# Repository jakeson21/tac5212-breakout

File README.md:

# tac5212_breakout
Breakout board for TAC5212

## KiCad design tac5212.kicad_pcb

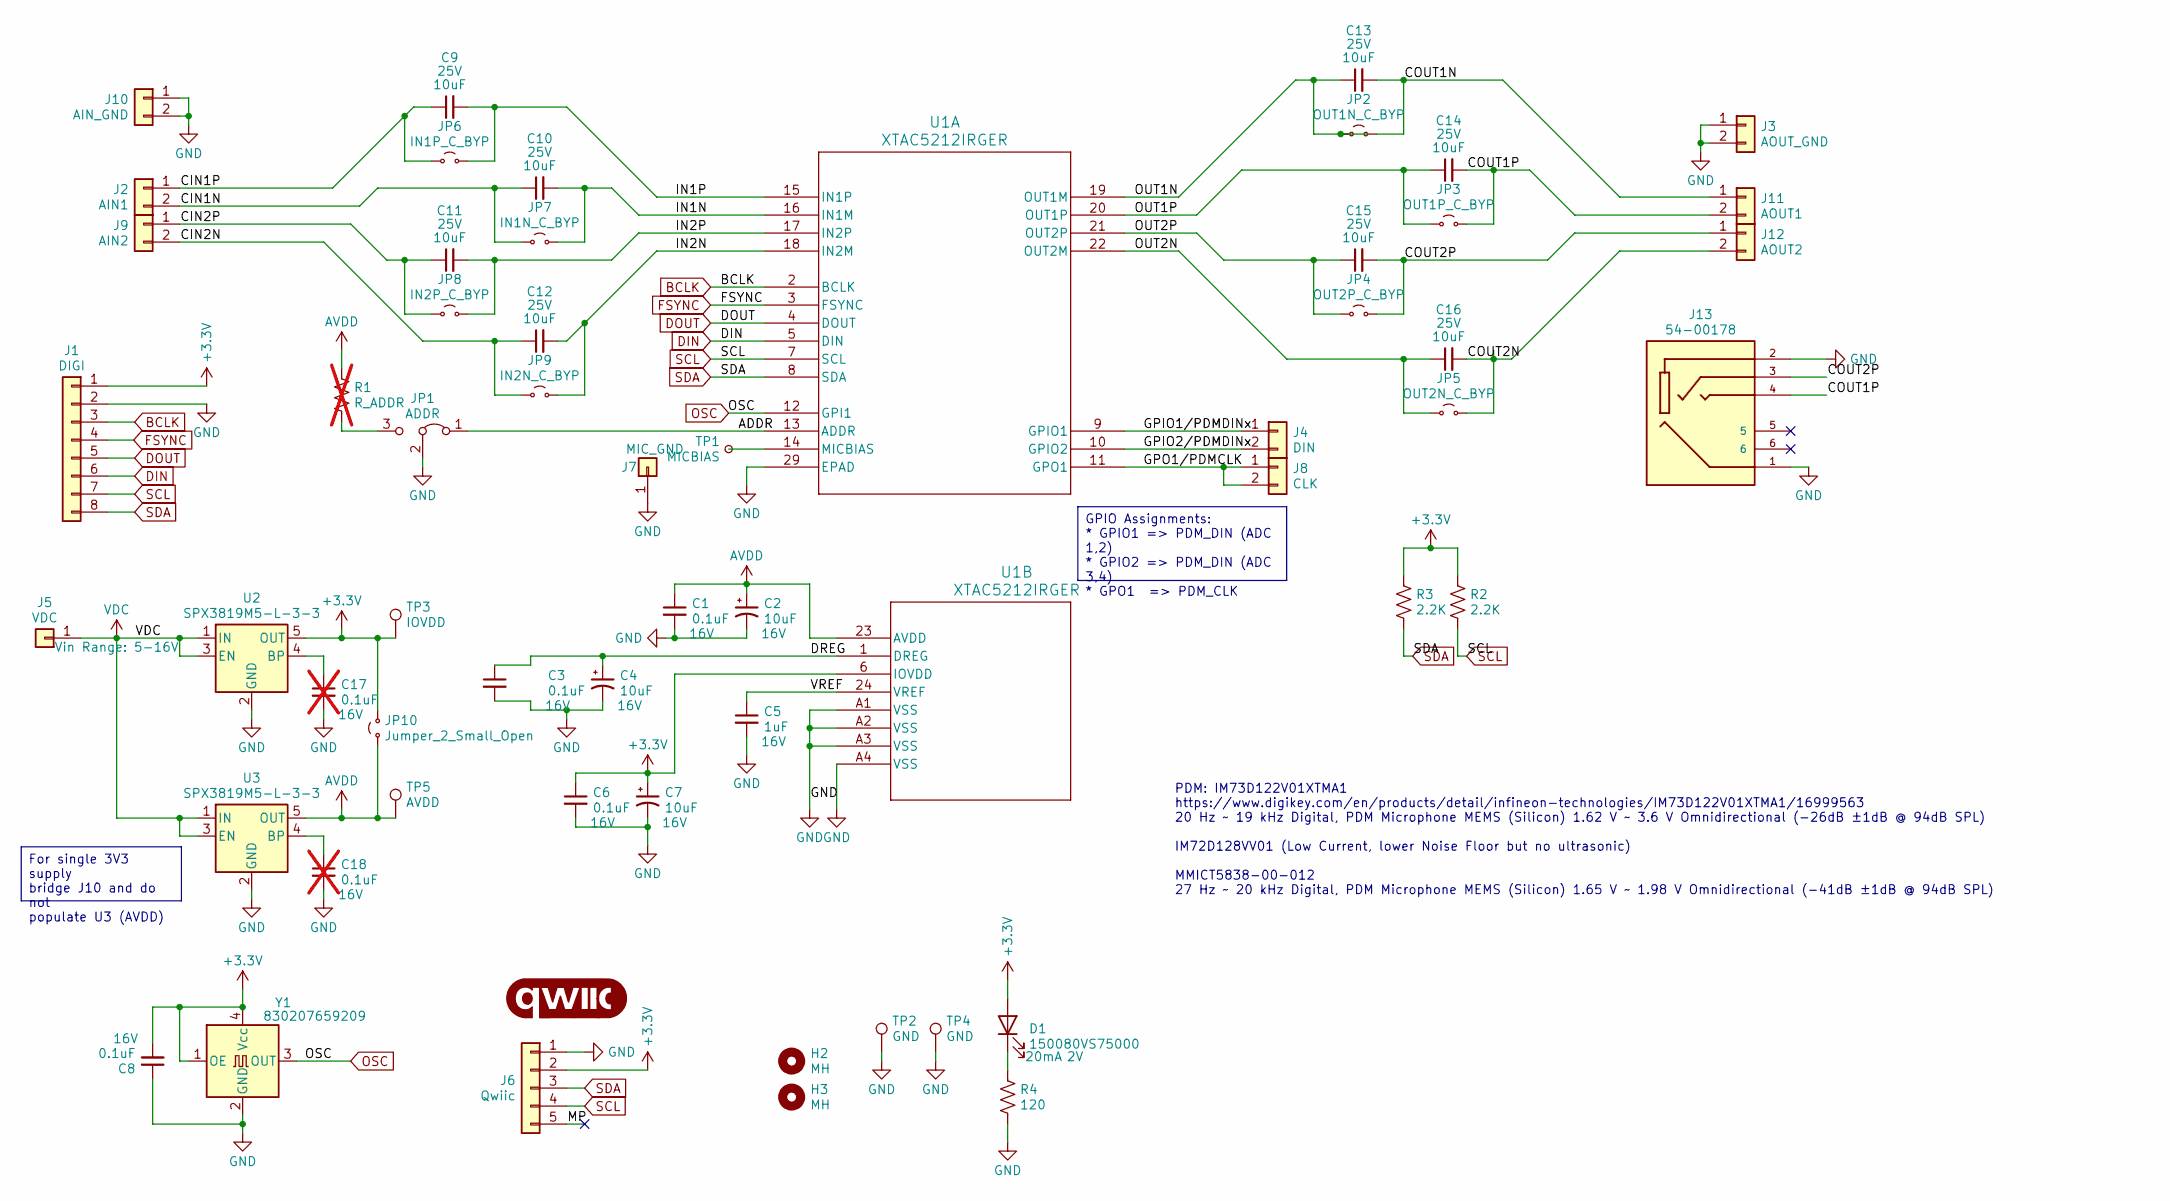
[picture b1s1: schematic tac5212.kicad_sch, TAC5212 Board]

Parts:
C1, C3, C6, C8: 0.1uF; C_0805_2012Metric
C2, C4, C7: 10uF; CP_EIA-3216-10_Kemet-I
C5: 1uF; C_0805_2012Metric
C9, C10, C11, C12, C13, C14, C15, C16: 10uF; C_0805_2012Metric
C17, C18: 0.1uF; C_0805_2012Metric; not fitted
D1: 150080VS75000; LED_0805_2012Metric
G1: qwiic_Logo
H2, H3: MH; MountingHole_2.2mm_M2
J1: DIGI; PinHeader_1x08_P2.54mm_Vertical
J2: AIN1; PinHeader_1x02_P2.54mm_Vertical
J3: AOUT_GND; PinHeader_1x02_P2.54mm_Vertical
J4: DIN; PinHeader_1x02_P2.54mm_Vertical
J5: VDC; PinHeader_1x01_P2.54mm_Vertical
J6: Qwiic; JST_SH_SM04B-SRSS-TB_1x04-1MP_P1.00mm_Horizontal
J7: MIC_GND; PinHeader_1x01_P2.54mm_Vertical
J8: CLK; PinHeader_1x02_P2.54mm_Vertical
J9: AIN2; PinHeader_1x02_P2.54mm_Vertical
J10: AIN_GND; PinHeader_1x02_P2.54mm_Vertical
J11: AOUT1; PinHeader_1x02_P2.54mm_Vertical
J12: AOUT2; PinHeader_1x02_P2.54mm_Vertical
J13: 54-00178; TENSILITY_54-00178; PARTREV A
JP1: ADDR; SolderJumper-3_P1.3mm_Bridged12_RoundedPad1.0x1.5mm_NumberL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
JP2: OUT1N_C_BYP; PinHeader_1x02_P2.54mm_Vertical
JP3: OUT1P_C_BYP; PinHeader_1x02_P2.54mm_Vertical
JP4: OUT2P_C_BYP; PinHeader_1x02_P2.54mm_Vertical
JP5: OUT2N_C_BYP; PinHeader_1x02_P2.54mm_Vertical
JP6: IN1P_C_BYP; PinHeader_1x02_P2.54mm_Vertical
JP7: IN1N_C_BYP; PinHeader_1x02_P2.54mm_Vertical
JP8: IN2P_C_BYP; PinHeader_1x02_P2.54mm_Vertical
JP9: IN2N_C_BYP; PinHeader_1x02_P2.54mm_Vertical
JP10: Jumper_2_Small_Open; SolderJumper-2_P1.3mm_Open_TrianglePad1.0x1.5mm
R1: R_ADDR; R_0805_2012Metric; not fitted
R2, R3: 2.2K; R_0805_2012Metric
R4: 120; R_0805_2012Metric
TP1: MICBIAS; TestPoint_THTPad_D1.5mm_Drill0.7mm
TP2, TP4: GND; 1030
TP3: IOVDD; TestPoint_THTPad_D1.0mm_Drill0.5mm
TP5: AVDD; TestPoint_THTPad_D1.0mm_Drill0.5mm
U1: XTAC5212IRGER; VQFN24_RGE_CORNERPADS_TEX
U2, U3: SPX3819M5-L-3-3; SOT-23-5
Y1: 830207659209; Oscillator_SMD_SeikoEpson_SG8002CE-4Pin_3.2x2.5mm

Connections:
+3.3V: C6.1, C7.1, C8.2, D1.2 (A), J1.1, J6.2, JP10.2 (B), R2.1, R3.1, TP3.1, U1.6 (IOVDD), U2.5 (OUT), Y1.1 (OE), Y1.4 (Vcc)
/ADDR: JP1.1 (A), U1.13 (ADDR)
/CIN1N: C10.1, J2.2, JP7.1 (A)
/CIN1P: C9.1, J2.1, JP6.1 (A)
/CIN2N: C12.1, J9.2, JP9.1 (A)
/CIN2P: C11.1, J9.1, JP8.1 (A)
/COUT1N: C13.2, J11.1, JP2.2 (B)
/COUT1P: C14.2, J11.2, J13.4, JP3.2 (B)
/COUT2N: C16.2, J12.2, JP5.2 (B)
/COUT2P: C15.2, J12.1, J13.3, JP4.2 (B)
/DREG: C3.1, C4.1, U1.1 (DREG)
/GPIO1/PDMDINx: J4.1, U1.9 (GPIO1)
/GPIO2/PDMDINx: J4.2, U1.10 (GPIO2)
/GPO1/PDMCLK: J8.1, J8.2, U1.11 (GPO1)
/IN1N: C10.2, JP7.2 (B), U1.16 (IN1M)
/IN1P: C9.2, JP6.2 (B), U1.15 (IN1P)
/IN2N: C12.2, JP9.2 (B), U1.18 (IN2M)
/IN2P: C11.2, JP8.2 (B), U1.17 (IN2P)
/OUT1N: C13.1, JP2.1 (A), U1.19 (OUT1M)
/OUT1P: C14.1, JP3.1 (A), U1.20 (OUT1P)
/OUT2N: C16.1, JP5.1 (A), U1.22 (OUT2M)
/OUT2P: C15.1, JP4.1 (A), U1.21 (OUT2P)
/VREF: C5.1, U1.24 (VREF)
AVDD: C1.1, C2.1, JP10.1 (A), R1.1, TP5.1, U1.23 (AVDD), U3.5 (OUT)
BCLK: J1.3, U1.2 (BCLK)
DIN: J1.6, U1.5 (DIN)
DOUT: J1.5, U1.4 (DOUT)
FSYNC: J1.4, U1.3 (FSYNC)
GND: C1.2, C2.2, C3.2, C4.2, C5.2, C6.2, C7.2, C8.1, C17.2, C18.2, J1.2, J3.1, J3.2, J6.1, J7.1, J10.1, J10.2, J13.1, J13.2, JP1.2 (C), R4.2, TP2.1, TP4.1, U1.29 (EPAD), U1.A1 (VSS), U1.A2 (VSS), U1.A3 (VSS), U1.A4 (VSS), U2.2 (GND), U3.2 (GND), Y1.2 (GND)
unnamed: D1.1 (K), R4.1
unnamed: JP1.3 (B), R1.2
unnamed: TP1.1, U1.14 (MICBIAS)
unnamed: C17.1, U2.4 (BP)
unnamed: C18.1, U3.4 (BP)
OSC: U1.12 (GPI1), Y1.3 (OUT)
SCL: J1.7, J6.4, R2.2, U1.7 (SCL)
SDA: J1.8, J6.3, R3.2, U1.8 (SDA)
VDC: J5.1, U2.1 (IN), U2.3 (EN), U3.1 (IN), U3.3 (EN)

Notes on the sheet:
PDM: IM73D122V01XTMA1 https://www.digikey.com/en/products/detail/infineon-technologies/IM73D122V01XTMA1/16999563 20 Hz ~ 19 kHz Digital, PDM Microphone MEMS (Silicon) 1.62 V ~ 3.6 V Omnidirectional (-26dB ±1dB @ 94dB SPL) IM72D128VV01 (Low Current, lower Noise Floor but no ultrasonic) MMICT5838-00-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
For single 3V3 supply bridge J10 and do not populate U3 (AVDD)
GPIO Assignments: * GPIO1 => PDM_DIN (ADC 1,2) * GPIO2 => PDM_DIN (ADC 3,4) * GPO1 => PDM_CLK

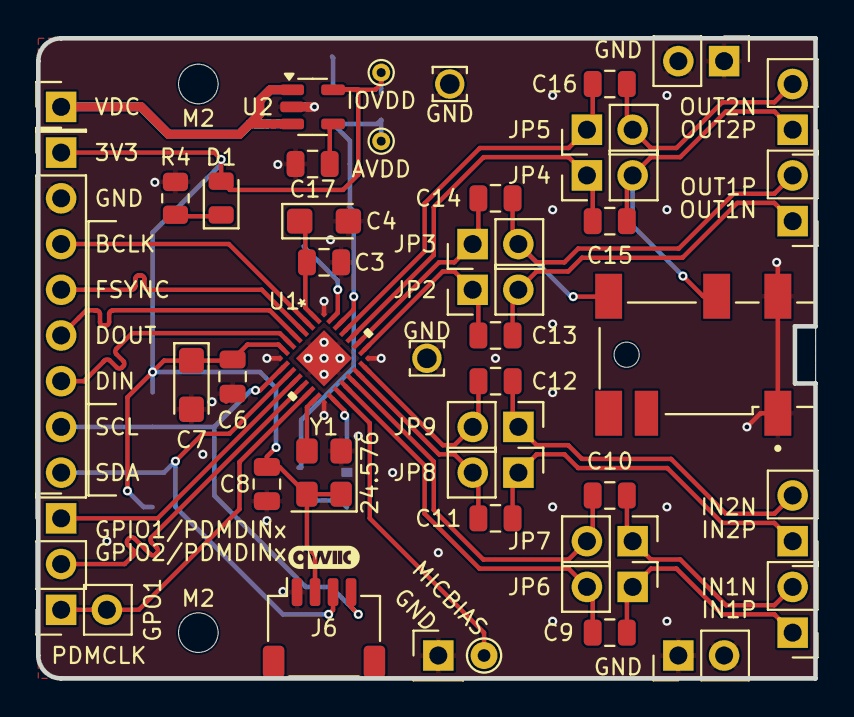
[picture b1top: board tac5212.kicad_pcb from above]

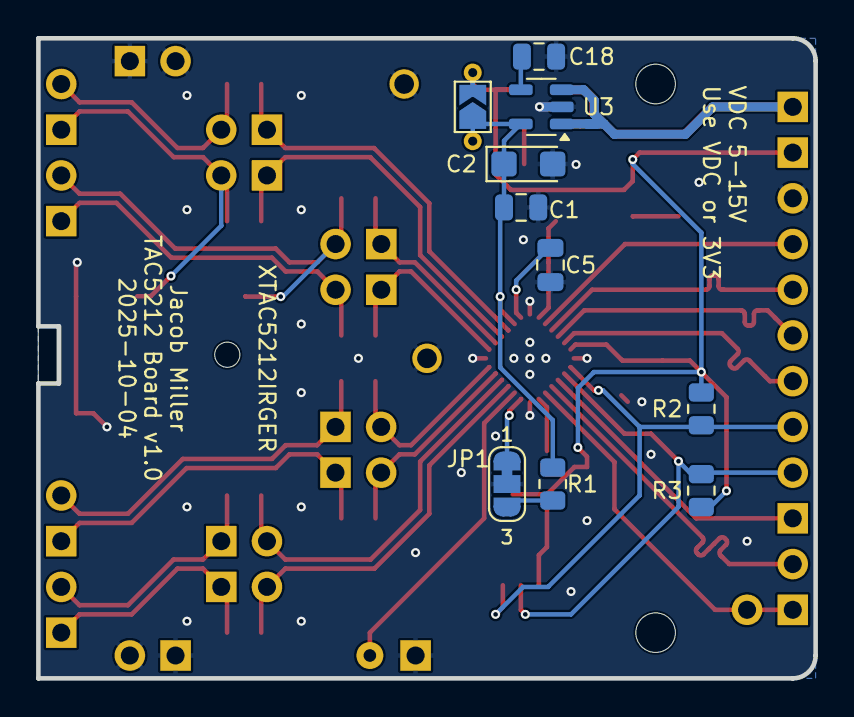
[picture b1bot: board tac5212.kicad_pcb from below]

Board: 4 copper layers, 43.2 x 35.6 mm, 57 parts (10 on the bottom side), 38 nets.

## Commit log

2025-10-05 v1.0 sent to fab - added AVDD supply
2025-10-28 add HTML BOM
